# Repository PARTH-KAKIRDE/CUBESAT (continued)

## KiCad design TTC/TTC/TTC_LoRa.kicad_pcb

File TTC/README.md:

# TTC — Telemetry, Tracking & Command

Radio (communications) module for the 2U CubeSat, LoRa version, Rev A.

## Overview
An STM32F446RET6 (same MCU and footprint as ADCS) drives an RFM98W LoRa module (Semtech SX1278) at 435–438 MHz. It sends telemetry to the ground station (a LilyGO LoRa board running TinyGS), receives commands, and passes data to and from the OBC over I²C (same connector and pins as ADCS) or UART. Power comes from the EPS 3.3 V or 5 V rail (JST-XH, as on ADCS).

The antenna output is either an SMA connector (default) or an LC balun feeding a dipole; fit one of the 0 Ω links R18 or R19.

**Status:** schematic complete. PCB is 85 × 84 mm, 2-layer, **fully routed** (KiCad DRC: 0 violations, 0 unconnected, schematic parity clean). Outline and four 4 mm mounting holes (74 mm × 76 mm pitch, 5.5 mm from the left/right edges and 4 mm from the top/bottom edges) follow the hand-measured drawing and match ADCS and EPS so the boards stack. Design rules are set to JLCPCB standard 2-layer limits (0.127 mm track/space). Not yet checked in 3D for assembly or ordered.

## Layout
- **Floorplan by function.** Power is bottom-left at the J1/J7 inputs. The MCU is centre-left beside the J8 header. The RFM98W radio and its antenna chain sit on the right edge at J3 (SMA) and J9 (dipole). I/O protection parts are directly above J2/J5/J6, and the temperature sensor sits between the MCU and the radio.
- **Spaced for hand soldering and probing.** The median gap to the nearest part is about 2 mm, with about 3 mm around the MCU, radio module and debug pad.
- **Critical paths.** The antenna path is 36 mm long, on the top layer only, with no vias. Each crystal sits next to its MCU pins with its tracks uncrossed, and each decoupling capacitor is at its supply pin.
- **Tracks.** Signals are 0.15 mm, power 0.3 mm, and +3V3 0.2 mm (so it can leave the 0.5 mm-pitch MCU pins). The RF tracks are 0.6 mm.
- **Ground.** GND is poured on both layers, with about 160 stitching vias. Surface-mount GND pads connect solidly to the pour (good for machine assembly, slower to hand-solder).
- **Manufacturing.** There is no top-layer copper under the RFM98W module. The board has 3 fiducials for machine assembly, and teardrops on every pad and via except the fine-pitch U3/U4 pins.

## History
This branch's git history keeps every earlier layout. To get one back, check out that commit's `TTC/TTC_LoRa.kicad_pcb` (or `TTC_auto/TTC_auto.kicad_pcb` for the auto-layout commits).
- `23c6f7e`: first fully routed layout (hand-placed).
- `d20aa38`: the same layout with the crystal re-routed.
- `16187b9`: the same layout with teardrops and antenna-path vias added.
- `f9c4dad`, `deac0fd`, `b9867ab`: auto-placed and auto-routed layouts. The current board is `b9867ab`.

## Contents
- `TTC_LoRa.kicad_sch`: schematic
- `TTC_LoRa.kicad_pcb`: PCB layout (routed)
- `TTC_LoRa.kicad_pro`: project configuration
- `TTC_LoRa.pdf`: schematic PDF export
- `TTC.kicad_sym`, `Library.pretty/`, `sym-lib-table`, `fp-lib-table`: project libraries (TPS7A2033 symbol, Tag-Connect footprint) needed to open the project

## Tool
Designed in KiCad 10. Open `TTC_LoRa.kicad_pro` to view the full project.

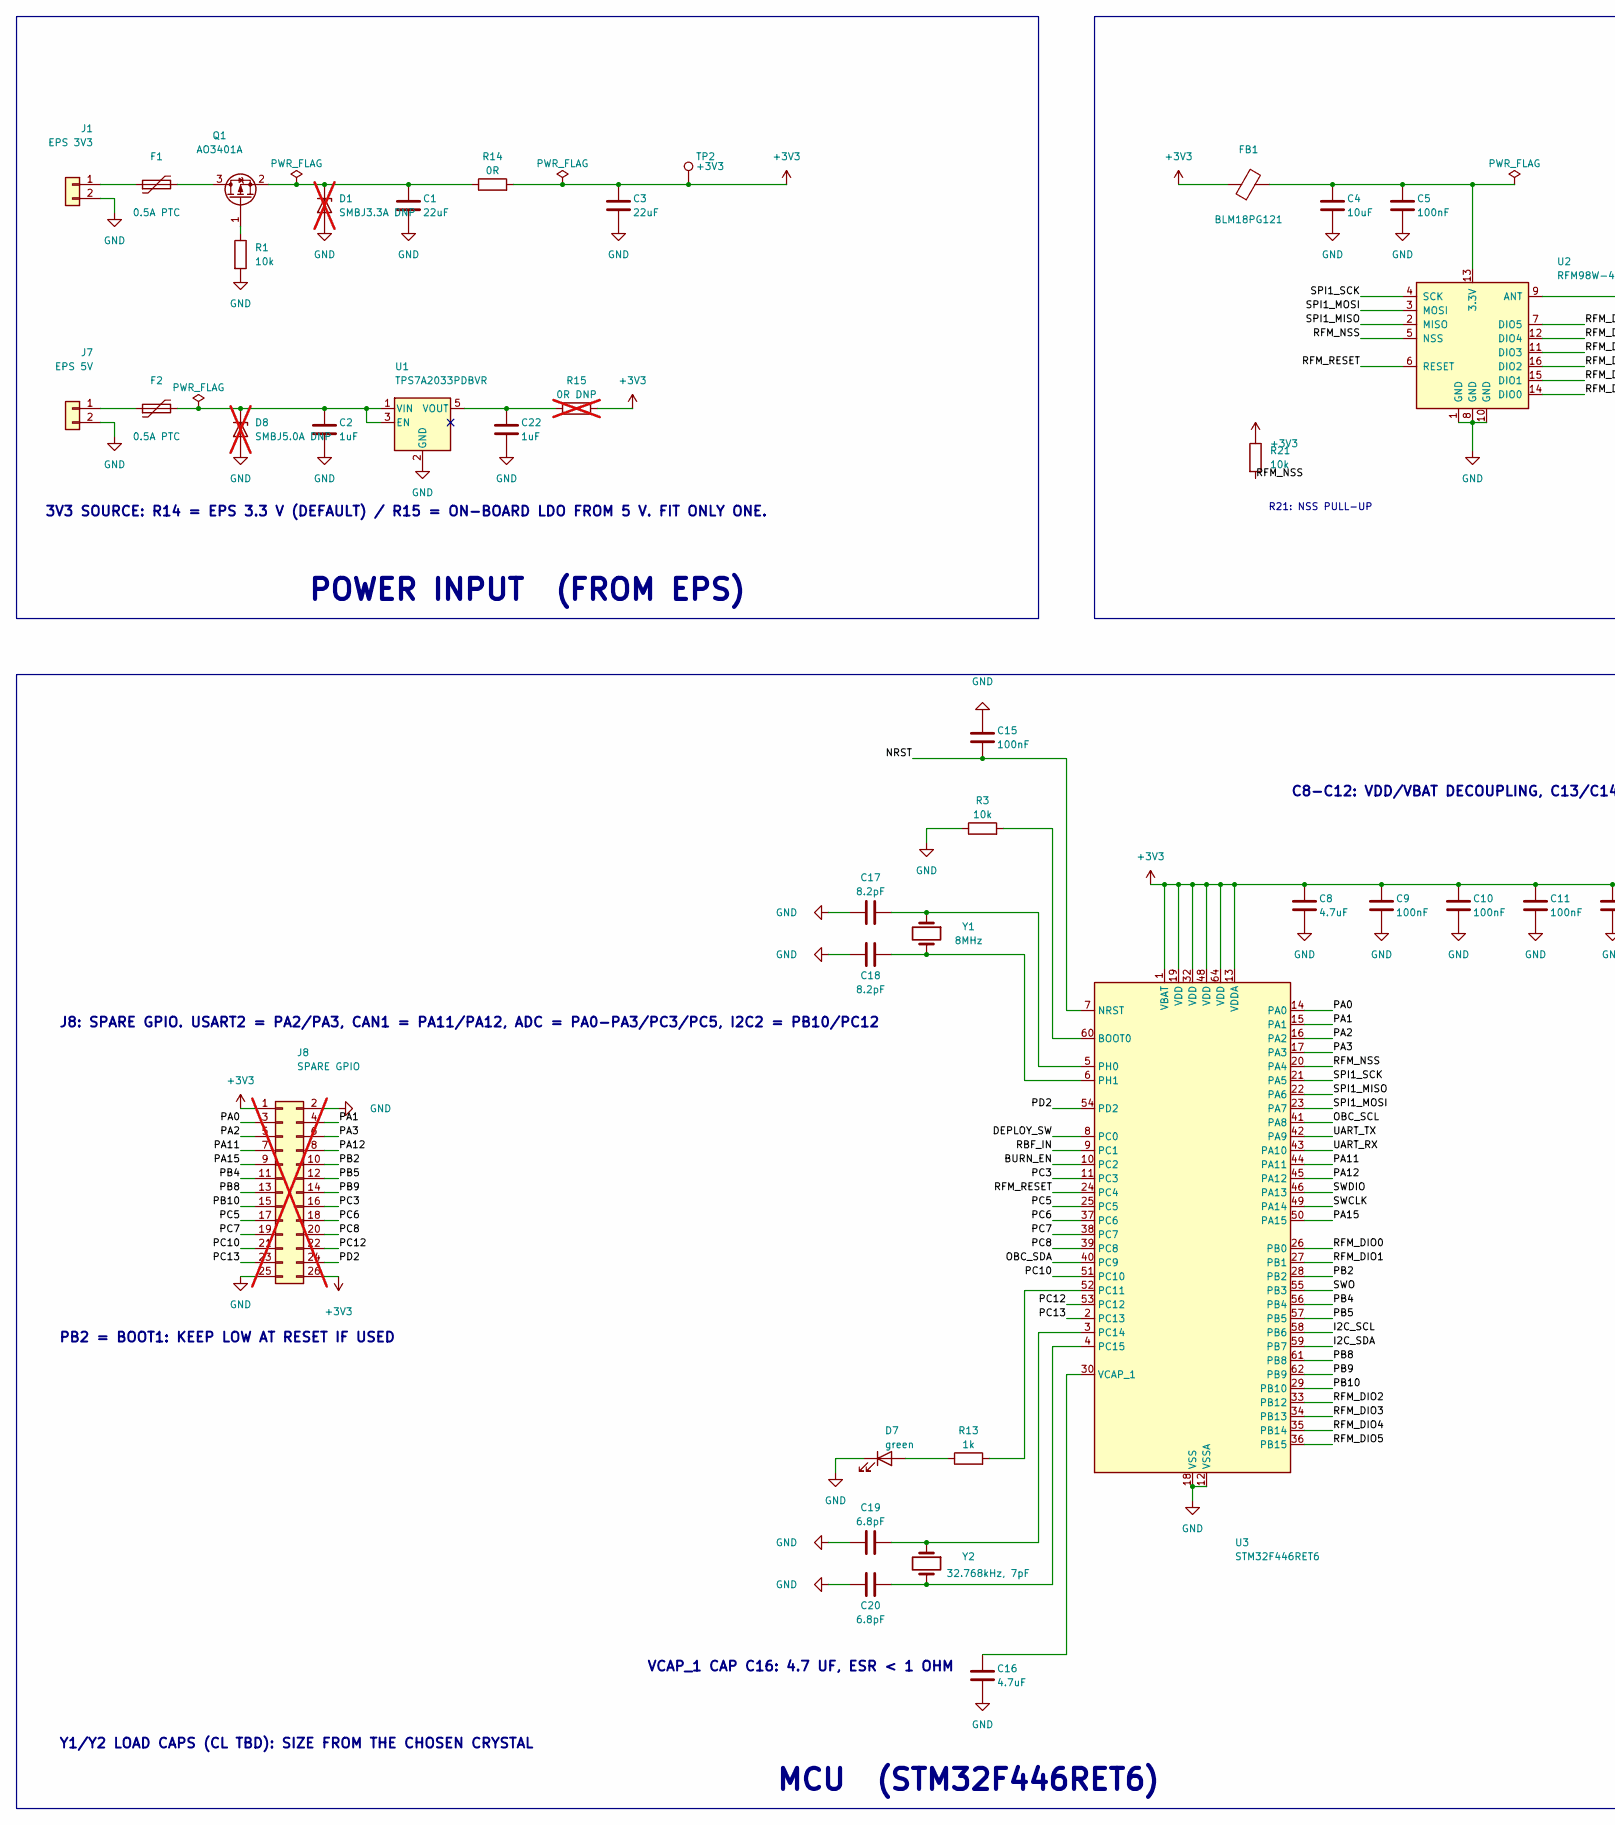
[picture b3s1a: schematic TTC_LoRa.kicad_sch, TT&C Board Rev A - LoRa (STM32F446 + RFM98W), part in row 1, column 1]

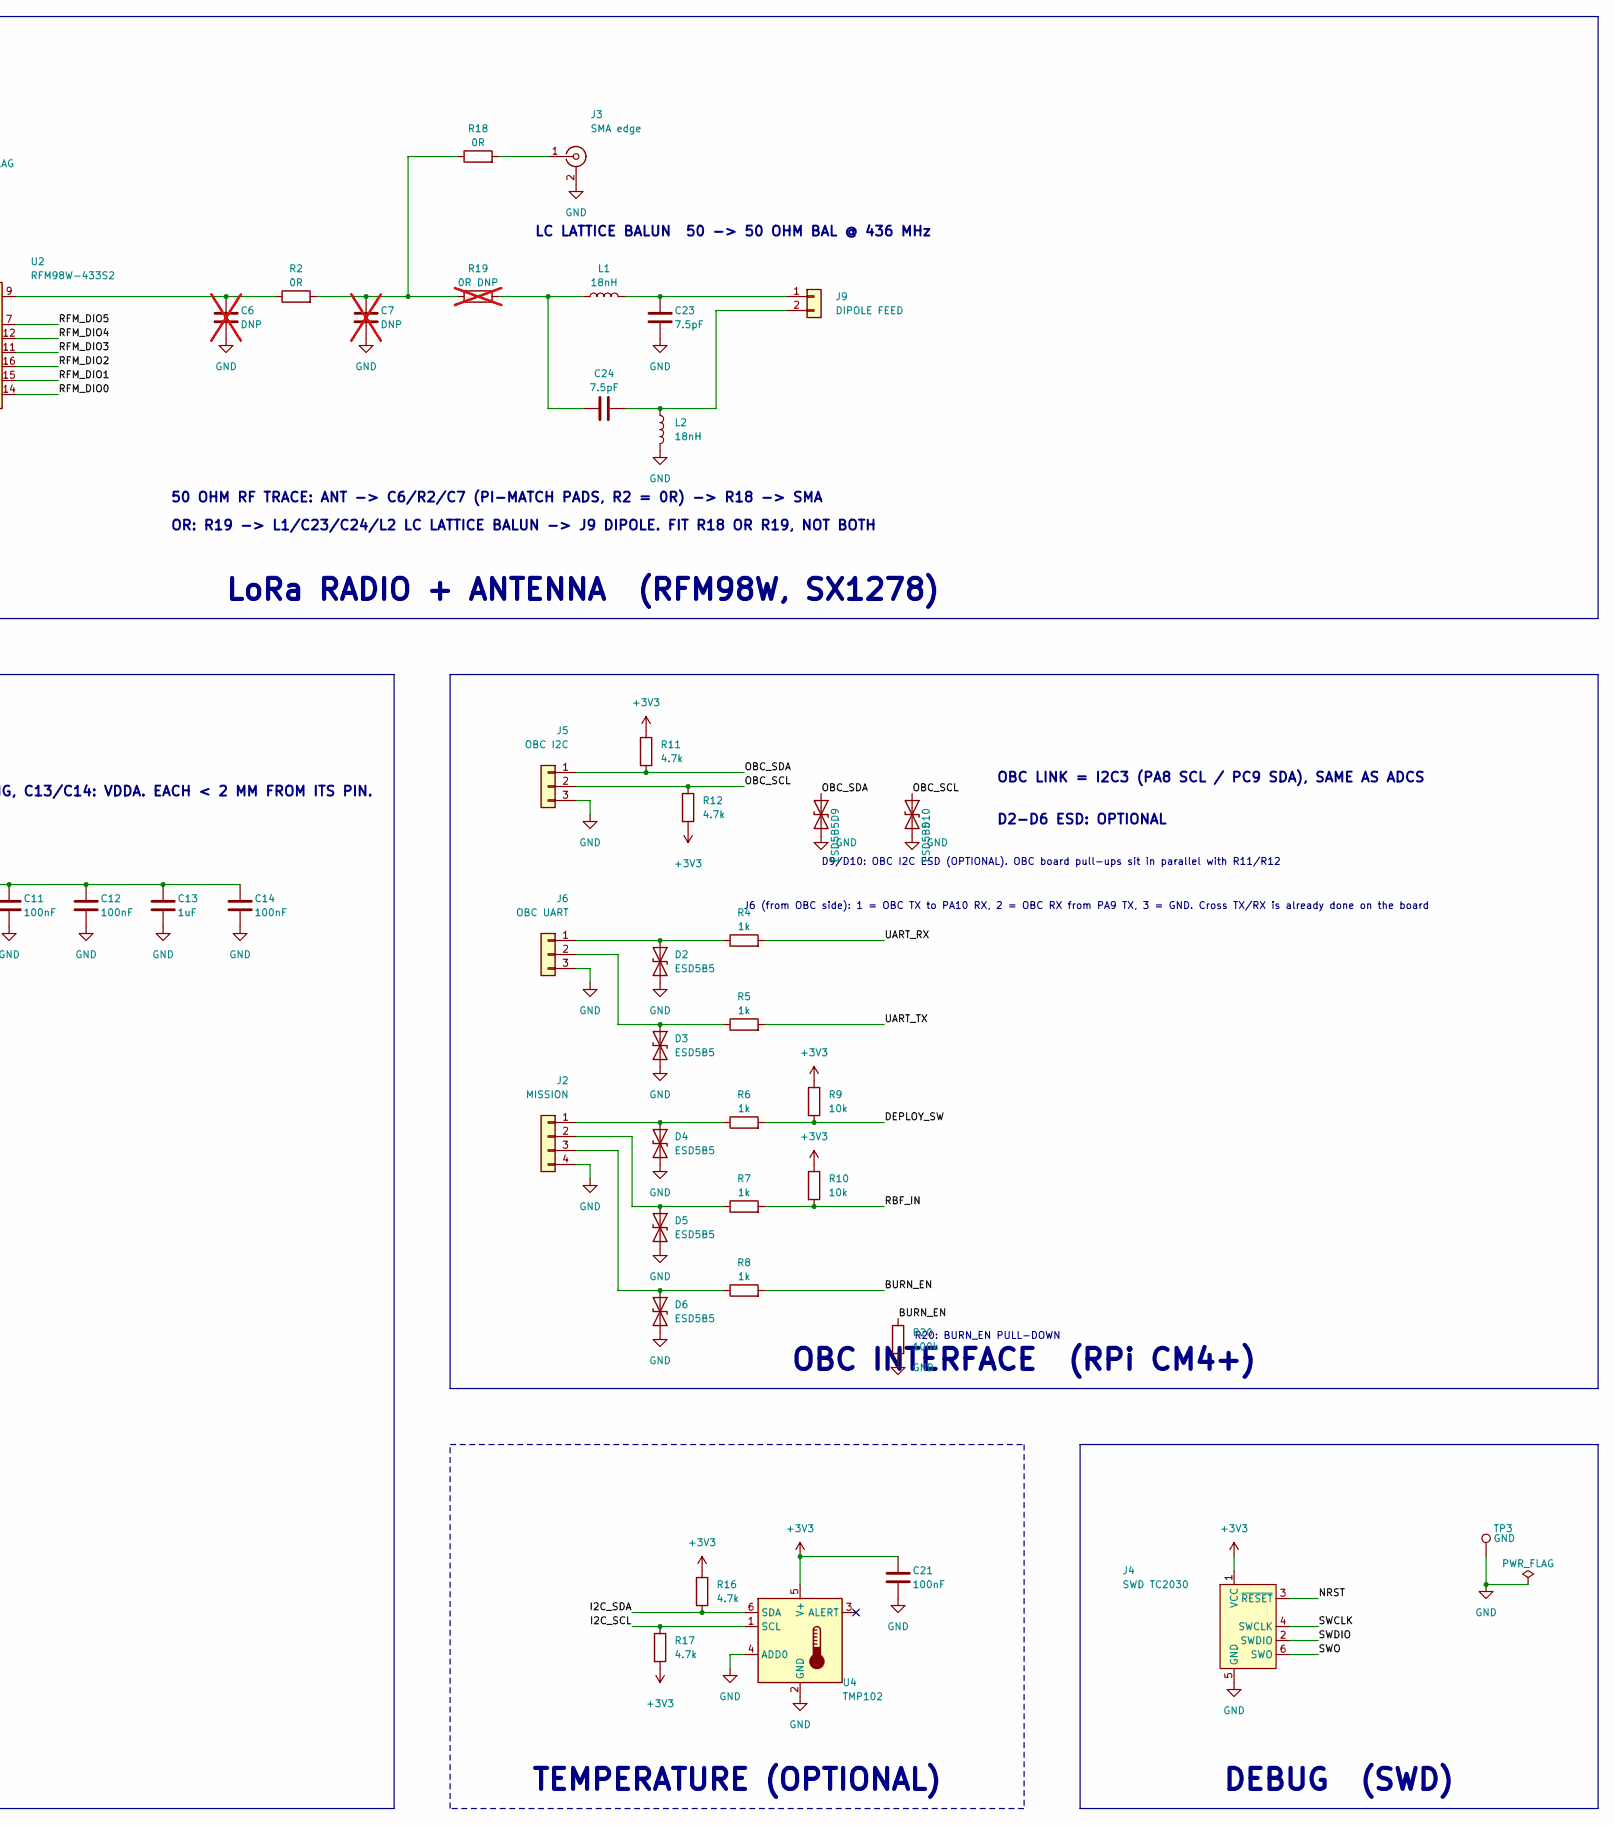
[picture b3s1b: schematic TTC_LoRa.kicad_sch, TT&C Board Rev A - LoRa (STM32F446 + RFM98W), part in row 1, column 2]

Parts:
C1, C3: 22uF; C_1206_3216Metric; Voltage 10V X7R
C2, C22: 1uF; C_0603_1608Metric; Voltage 16V X7R
C4: 10uF; C_0805_2012Metric; Voltage 10V X7R
C5, C21: 100nF; C_0402_1005Metric
C6, C7: DNP; C_0402_1005Metric; not fitted
C8: 4.7uF; C_0603_1608Metric
C9, C10, C11, C12, C14, C15: 100nF; C_0603_1608Metric
C13: 1uF; C_0603_1608Metric
C16: 4.7uF; C_0603_1608Metric; Voltage 10V X7R
C17, C18: 8.2pF; C_0603_1608Metric
C19, C20: 6.8pF; C_0603_1608Metric
C23, C24: 7.5pF; C_0402_1005Metric; Voltage 50V C0G; MPN Murata GJM1555C1H7R5BB01D
D1: SMBJ3.3A DNP; D_SMB; not fitted
D2, D3, D4, D5, D6, D9, D10: ESD5B5; D_SOD-523
D7: green; LED_0603_1608Metric
D8: SMBJ5.0A DNP; D_SMB; not fitted
F1, F2: 0.5A PTC; Fuse_1206_3216Metric
FB1: BLM18PG121; L_0603_1608Metric
J1: EPS 3V3; JST_XH_B2B-XH-AM_1x02_P2.50mm_Vertical
J2: MISSION; JST_PH_B4B-PH-K_1x04_P2.00mm_Vertical
J3: SMA edge; SMA_Samtec_SMA-J-P-H-ST-EM1_EdgeMount
J4: SWD TC2030; Tag-Connect_TC2030-IDC-NL_2x03_P1.27mm_Vertical
J5: OBC I2C; JST_PH_B3B-PH-K_1x03_P2.00mm_Vertical
J6: OBC UART; JST_PH_B3B-PH-K_1x03_P2.00mm_Vertical
J7: EPS 5V; JST_XH_B2B-XH-AM_1x02_P2.50mm_Vertical
J8: SPARE GPIO; PinHeader_2x13_P2.54mm_Vertical; not fitted
J9: DIPOLE FEED; SolderWire-0.25sqmm_1x02_P4.2mm_D0.65mm_OD1.7mm
L1, L2: 18nH; L_0603_1608Metric; MPN Coilcraft 0603HP-18NXGLW / Murata LQW18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
Q1: AO3401A; SOT-23
R1, R3, R9, R10, R21: 10k; R_0603_1608Metric
R2, R18: 0R; R_0402_1005Metric
R4, R5, R6, R7, R8, R13: 1k; R_0603_1608Metric
R11, R12, R16, R17: 4.7k; R_0603_1608Metric
R14: 0R; R_0603_1608Metric
R15: 0R DNP; R_0603_1608Metric; not fitted
R19: 0R DNP; R_0402_1005Metric; not fitted
R20: 100k; R_0603_1608Metric
TP2: +3V3; TestPoint_Pad_D1.5mm
TP3: GND; TestPoint_Pad_D1.5mm
U1: TPS7A2033PDBVR; SOT-23-5
U2: RFM98W-433S2; HOPERF_RFM9XW_SMD
U3: STM32F446RET6; LQFP-64_10x10mm_P0.5mm
U4: TMP102; SOT-563
Y1: 8MHz; Crystal_SMD_5032-2Pin_5.0x3.2mm
Y2: 32.768kHz, 7pF; Crystal_SMD_3215-2Pin_3.2x1.5mm

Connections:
+3V3: C3.1, C8.1, C9.1, C10.1, C11.1, C12.1, C13.1, C14.1, C21.1, FB1.1, J4.1 (VCC), J8.1, J8.26, R9.1, R10.1, R11.1, R12.2, R14.2, R15.2, R16.1, R17.2, R21.1, TP2.1, U3.1 (VBAT), U3.13 (VDDA), U3.19 (VDD), U3.32 (VDD), U3.48 (VDD), U3.64 (VDD), U4.5 (V+)
/BURN_EN: R8.2, R20.1, U3.10 (PC2)
/DEPLOY_SW: R6.2, R9.2, U3.8 (PC0)
/I2C_SCL: R17.1, U3.58 (PB6), U4.1 (SCL)
/I2C_SDA: R16.2, U3.59 (PB7), U4.6 (SDA)
/NRST: C15.2, J4.3 (~RESET), U3.7 (NRST)
/OBC_SCL: D10.1 (A1), J5.2, R12.1, U3.41 (PA8)
/OBC_SDA: D9.1 (A1), J5.1, R11.2, U3.40 (PC9)
/PA0: J8.3, U3.14 (PA0)
/PA1: J8.4, U3.15 (PA1)
/PA2: J8.5, U3.16 (PA2)
/PA3: J8.6, U3.17 (PA3)
/PA11: J8.7, U3.44 (PA11)
/PA12: J8.8, U3.45 (PA12)
/PA15: J8.9, U3.50 (PA15)
/PB2: J8.10, U3.28 (PB2)
/PB4: J8.11, U3.56 (PB4)
/PB5: J8.12, U3.57 (PB5)
/PB8: J8.13, U3.61 (PB8)
/PB9: J8.14, U3.62 (PB9)
/PB10: J8.15, U3.29 (PB10)
/PC3: J8.16, U3.11 (PC3)
/PC5: J8.17, U3.25 (PC5)
/PC6: J8.18, U3.37 (PC6)
/PC7: J8.19, U3.38 (PC7)
/PC8: J8.20, U3.39 (PC8)
/PC10: J8.21, U3.51 (PC10)
/PC12: J8.22, U3.53 (PC12)
/PC13: J8.23, U3.2 (PC13)
/PD2: J8.24, U3.54 (PD2)
/RBF_IN: R7.2, R10.2, U3.9 (PC1)
/RFM_DIO0: U2.14 (DIO0), U3.26 (PB0)
/RFM_DIO1: U2.15 (DIO1), U3.27 (PB1)
/RFM_DIO2: U2.16 (DIO2), U3.33 (PB12)
/RFM_DIO3: U2.11 (DIO3), U3.34 (PB13)
/RFM_DIO4: U2.12 (DIO4), U3.35 (PB14)
/RFM_DIO5: U2.7 (DIO5), U3.36 (PB15)
/RFM_NSS: R21.2, U2.5 (NSS), U3.20 (PA4)
/RFM_RESET: U2.6 (RESET), U3.24 (PC4)
/SPI1_MISO: U2.2 (MISO), U3.22 (PA6)
/SPI1_MOSI: U2.3 (MOSI), U3.23 (PA7)
/SPI1_SCK: U2.4 (SCK), U3.21 (PA5)
/SWCLK: J4.4 (SWCLK), U3.49 (PA14)
/SWDIO: J4.2 (SWDIO), U3.46 (PA13)
/SWO: J4.6 (SWO), U3.55 (PB3)
/UART_RX: R4.2, U3.43 (PA10)
/UART_TX: R5.2, U3.42 (PA9)
GND: C1.2, C2.2, C3.2, C4.2, C5.2, C6.2, C7.2, C8.2, C9.2, C10.2, C11.2, C12.2, C13.2, C14.2, C15.1, C16.2, C17.1, C18.1, C19.1, C20.1, C21.2, C22.2, C23.2, D1.2 (A), D2.2 (A2), D3.2 (A2), D4.2 (A2), D5.2 (A2), D6.2 (A2), D7.1 (K), D8.2 (A), D9.2 (A2), D10.2 (A2), J1.2, J2.4, J3.2 (Ext), J4.5 (GND), J5.3, J6.3, J7.2, J8.2, J8.25, L2.2, R1.2, R3.1, R20.2, TP3.1, U1.2 (GND), U2.1 (GND), U2.8 (GND), U2.10 (GND), U3.12 (VSSA), U3.18 (VSS), U3.31 (VSS), U3.47 (VSS), U3.63 (VSS), U4.2 (GND), U4.4 (ADD0)
unnamed: C7.1, R2.2, R18.1, R19.1
unnamed: C24.1, L1.1, R19.2
unnamed: C1.1, D1.1 (K), Q1.2 (S), R14.1
unnamed: D2.1 (A1), J6.1, R4.1
unnamed: D3.1 (A1), J6.2, R5.1
unnamed: D4.1 (A1), J2.1, R6.1
unnamed: D5.1 (A1), J2.2, R7.1
unnamed: D6.1 (A1), J2.3, R8.1
unnamed: D7.2 (A), R13.1
unnamed: C2.1, D8.1 (K), F2.2, U1.1 (VIN), U1.3 (EN)
unnamed: F1.1, J1.1
unnamed: J3.1 (In), R18.2
unnamed: F2.1, J7.1
unnamed: C23.1, J9.1, L1.2
unnamed: C24.2, J9.2, L2.1
unnamed: F1.2, Q1.3 (D)
unnamed: Q1.1 (G), R1.1
unnamed: C22.1, R15.1, U1.5 (VOUT)
unnamed: C4.1, C5.1, FB1.2, U2.13 (3.3V)
unnamed: C6.1, R2.1, U2.9 (ANT)
unnamed: R3.2, U3.60 (BOOT0)
unnamed: R13.2, U3.52 (PC11)
unnamed: C19.2, U3.3 (PC14), Y2.1
unnamed: C20.2, U3.4 (PC15), Y2.2
unnamed: C17.2, U3.5 (PH0), Y1.1
unnamed: C18.2, U3.6 (PH1), Y1.2
unnamed: C16.1, U3.30 (VCAP_1)

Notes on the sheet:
LC LATTICE BALUN 50 -> 50 OHM BAL @ 436 MHz
TEMPERATURE (OPTIONAL)
3V3 SOURCE: R14 = EPS 3.3 V (DEFAULT) / R15 = ON-BOARD LDO FROM 5 V. FIT ONLY ONE.
POWER INPUT (FROM EPS)
Y1/Y2 LOAD CAPS (CL TBD): SIZE FROM THE CHOSEN CRYSTAL
DEBUG (SWD)
OR: R19 -> L1/C23/C24/L2 LC LATTICE BALUN -> J9 DIPOLE. FIT R18 OR R19, NOT BOTH
50 OHM RF TRACE: ANT -> C6/R2/C7 (PI-MATCH PADS, R2 = 0R) -> R18 -> SMA
R21: NSS PULL-UP
VCAP_1 CAP C16: 4.7 UF, ESR < 1 OHM
C8-C12: VDD/VBAT DECOUPLING, C13/C14: VDDA. EACH < 2 MM FROM ITS PIN.
OBC INTERFACE (RPi CM4+)
OBC LINK = I2C3 (PA8 SCL / PC9 SDA), SAME AS ADCS
LoRa RADIO + ANTENNA (RFM98W, SX1278)
PB2 = BOOT1: KEEP LOW AT RESET IF USED
R20: BURN_EN PULL-DOWN
J6 (from OBC side): 1 = OBC TX to PA10 RX, 2 = OBC RX from PA9 TX, 3 = GND. Cross TX/RX is already done on the board
MCU (STM32F446RET6)
J8: SPARE GPIO. USART2 = PA2/PA3, CAN1 = PA11/PA12, ADC = PA0-PA3/PC3/PC5, I2C2 = PB10/PC12
D2-D6 ESD: OPTIONAL
D9/D10: OBC I2C ESD (OPTIONAL). OBC board pull-ups sit in parallel with R11/R12

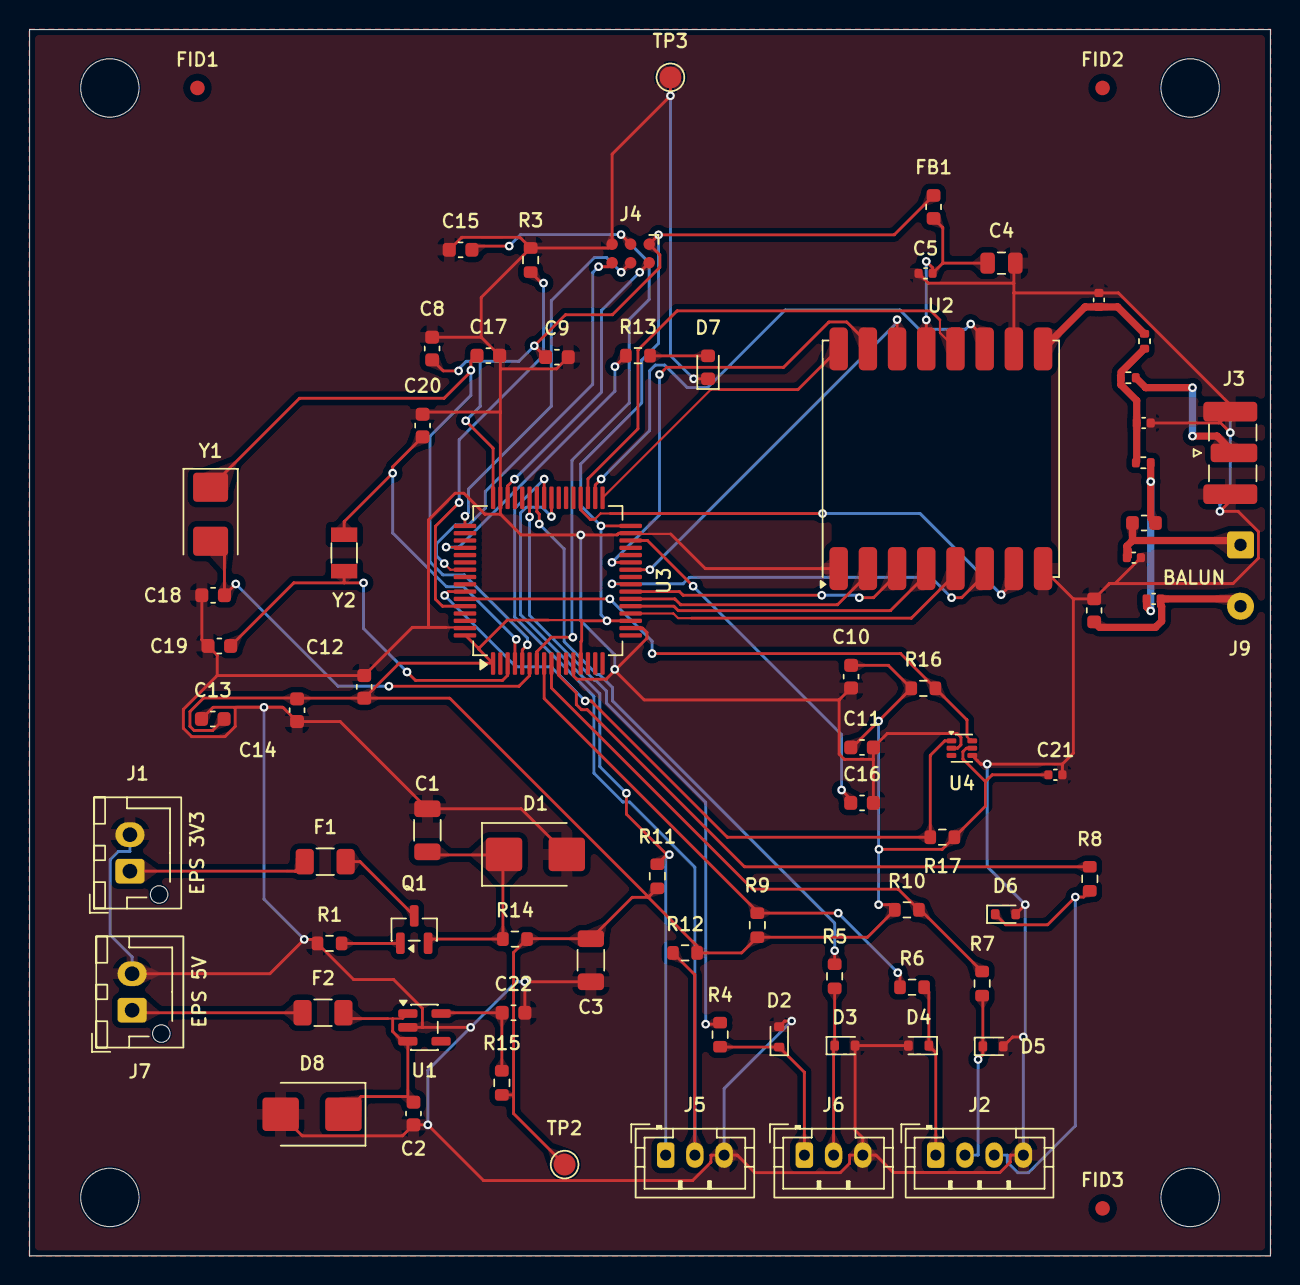
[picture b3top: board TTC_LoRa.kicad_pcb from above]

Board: 2 copper layers, 85.0 x 84.0 mm, 80 parts (0 on the bottom side), 53 nets.

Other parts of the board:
FID1, FID2, FID3: Fiducial; Fiducial_1mm_Mask2mm
H1, H2, H3, H4: M4 stack; MountingHole_4mm
